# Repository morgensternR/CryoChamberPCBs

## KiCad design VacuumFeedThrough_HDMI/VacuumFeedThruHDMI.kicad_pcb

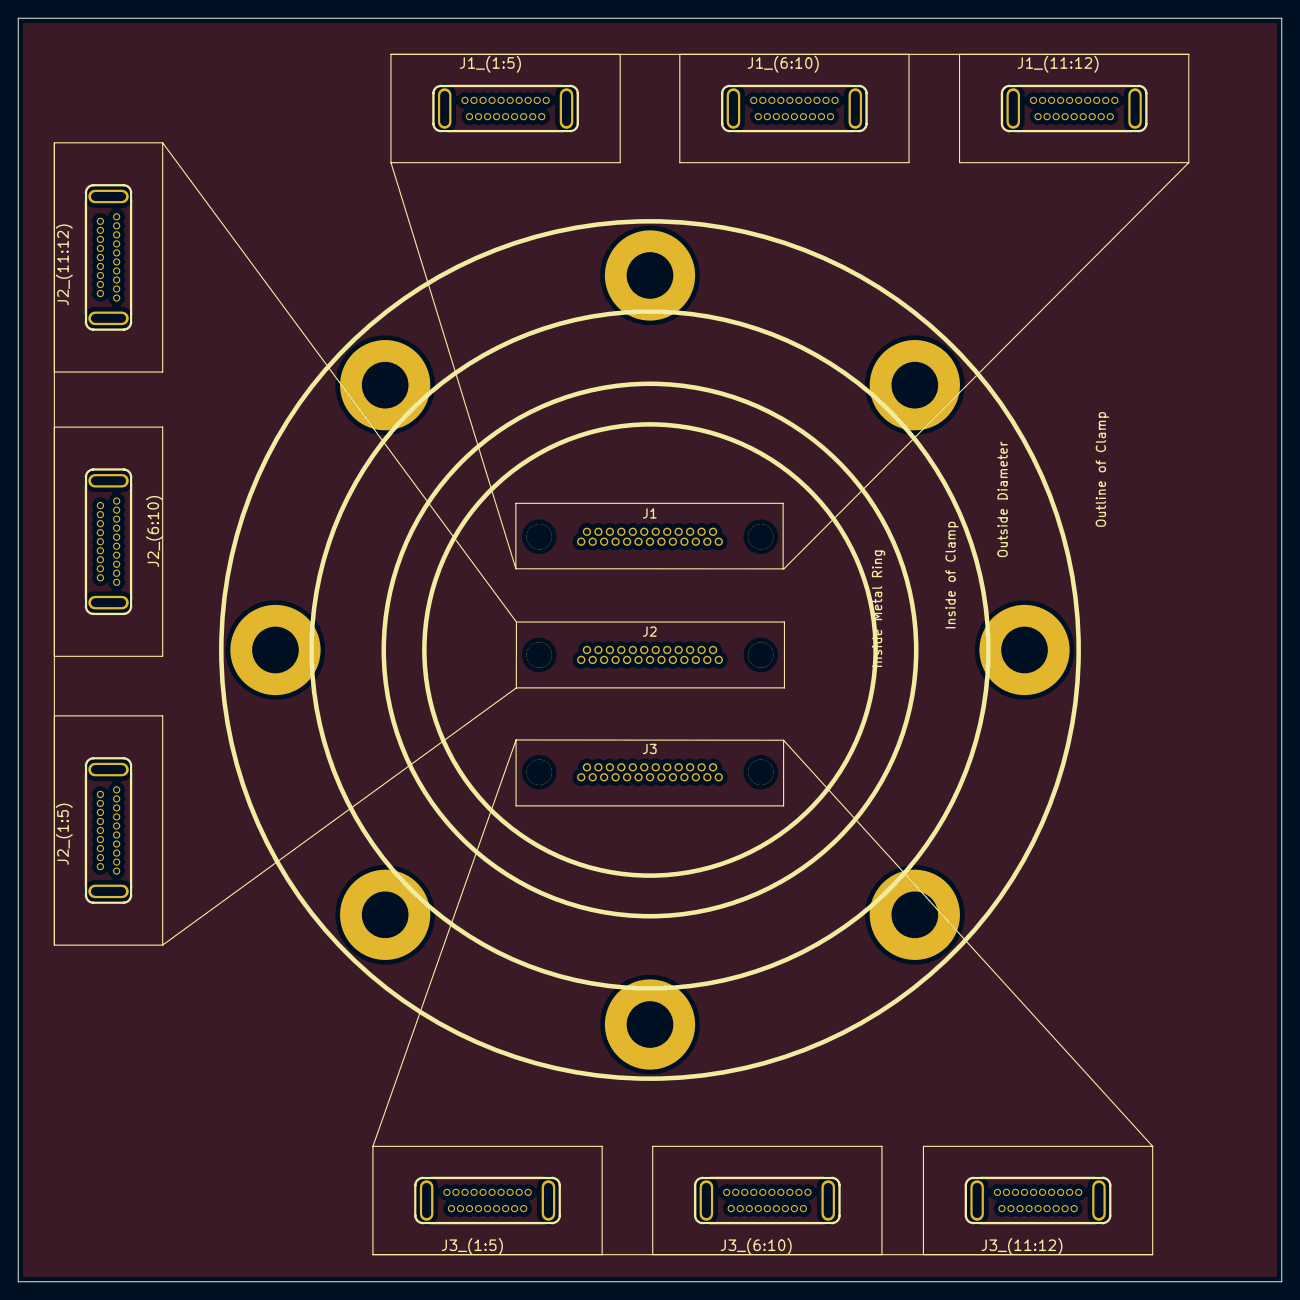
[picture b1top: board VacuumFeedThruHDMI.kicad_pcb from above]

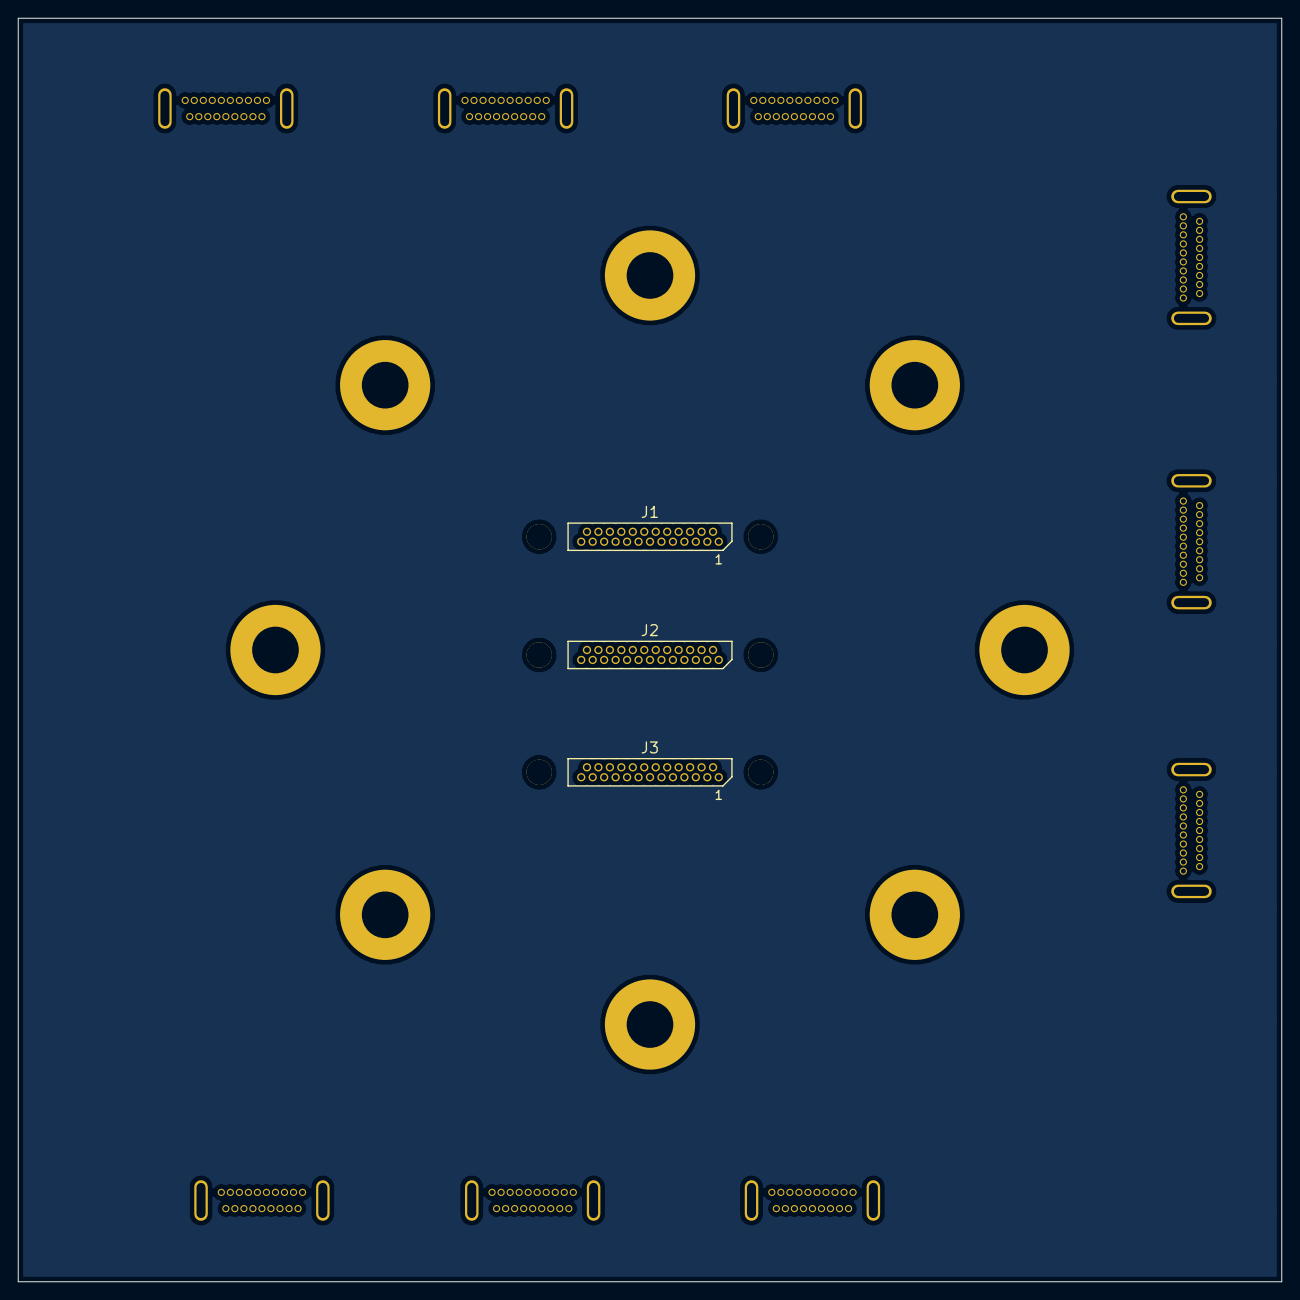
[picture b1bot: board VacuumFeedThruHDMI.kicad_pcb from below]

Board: 4 copper layers, 140.0 x 140.0 mm, 13 parts (3 on the bottom side), 73 nets.

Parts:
J1, J2#2, J3: DB25_Male; Norcomp-380-025-113L001-microd_NoLeads
J1_(1:5), J1_(6:10), J1_(11:12), J2_(1:5), J2_(6:10), J2_(11:12), J3_(1:5), J3_(6:10), J3_(11:12): HDMI_A_1.4; HDMI-Vertical-Male-JLBPCB
J2: Conn_01x08; KF50_Print

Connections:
unnamed: J1.6, J1_(6:10).1
unnamed: J1.19, J1_(6:10).3
unnamed: J1.7, J1_(6:10).4
unnamed: J1.20, J1_(6:10).6
unnamed: J1.8, J1_(6:10).7
unnamed: J1.21, J1_(6:10).9
unnamed: J1.9, J1_(6:10).10
unnamed: J1.22, J1_(6:10).12
unnamed: J1.10, J1_(6:10).14
unnamed: J1.23, J1_(6:10).19
unnamed: J1.1, J1_(1:5).1
unnamed: J1.14, J1_(1:5).3
unnamed: J1.2, J1_(1:5).4
unnamed: J1.15, J1_(1:5).6
unnamed: J1.3, J1_(1:5).7
unnamed: J1.16, J1_(1:5).9
unnamed: J1.4, J1_(1:5).10
unnamed: J1.17, J1_(1:5).12
unnamed: J1.5, J1_(1:5).14
unnamed: J1.18, J1_(1:5).19
unnamed: J1.11, J1_(11:12).1
unnamed: J1.24, J1_(11:12).3
unnamed: J1.12, J1_(11:12).4
unnamed: J1.25, J1_(11:12).6
unnamed: J2#2.6, J2_(6:10).1
unnamed: J2#2.19, J2_(6:10).3
unnamed: J2#2.7, J2_(6:10).4
unnamed: J2#2.20, J2_(6:10).6
unnamed: J2#2.8, J2_(6:10).7
unnamed: J2#2.21, J2_(6:10).9
unnamed: J2#2.9, J2_(6:10).10
unnamed: J2#2.22, J2_(6:10).12
unnamed: J2#2.10, J2_(6:10).14
unnamed: J2#2.23, J2_(6:10).19
unnamed: J2#2.1, J2_(1:5).1
unnamed: J2#2.14, J2_(1:5).3
unnamed: J2#2.2, J2_(1:5).4
unnamed: J2#2.15, J2_(1:5).6
unnamed: J2#2.3, J2_(1:5).7
unnamed: J2#2.16, J2_(1:5).9
unnamed: J2#2.4, J2_(1:5).10
unnamed: J2#2.17, J2_(1:5).12
unnamed: J2#2.5, J2_(1:5).14
unnamed: J2#2.18, J2_(1:5).19
unnamed: J2#2.11, J2_(11:12).1
unnamed: J2#2.24, J2_(11:12).3
unnamed: J2#2.12, J2_(11:12).4
unnamed: J2#2.25, J2_(11:12).6
unnamed: J3.1, J3_(1:5).1
unnamed: J3.14, J3_(1:5).3
unnamed: J3.2, J3_(1:5).4
unnamed: J3.15, J3_(1:5).6
unnamed: J3.3, J3_(1:5).7
unnamed: J3.16, J3_(1:5).9
unnamed: J3.4, J3_(1:5).10
unnamed: J3.17, J3_(1:5).12
unnamed: J3.5, J3_(1:5).14
unnamed: J3.18, J3_(1:5).19
unnamed: J3.11, J3_(11:12).1
unnamed: J3.24, J3_(11:12).3
unnamed: J3.12, J3_(11:12).4
unnamed: J3.25, J3_(11:12).6
unnamed: J3.6, J3_(6:10).1
unnamed: J3.7, J3_(6:10).4
unnamed: J3.8, J3_(6:10).7
unnamed: J3.9, J3_(6:10).10
unnamed: J3.10, J3_(6:10).14
unnamed: J3.19, J3_(6:10).3
unnamed: J3.20, J3_(6:10).6
unnamed: J3.21, J3_(6:10).9
unnamed: J3.22, J3_(6:10).12
unnamed: J3.23, J3_(6:10).19
unnamed: J2.1, J2.2, J2.3, J2.4, J2.5, J2.6, J2.7, J2.8
